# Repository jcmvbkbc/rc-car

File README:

RC car with bidirectional drive and servo steering, controlled by ESP8266.

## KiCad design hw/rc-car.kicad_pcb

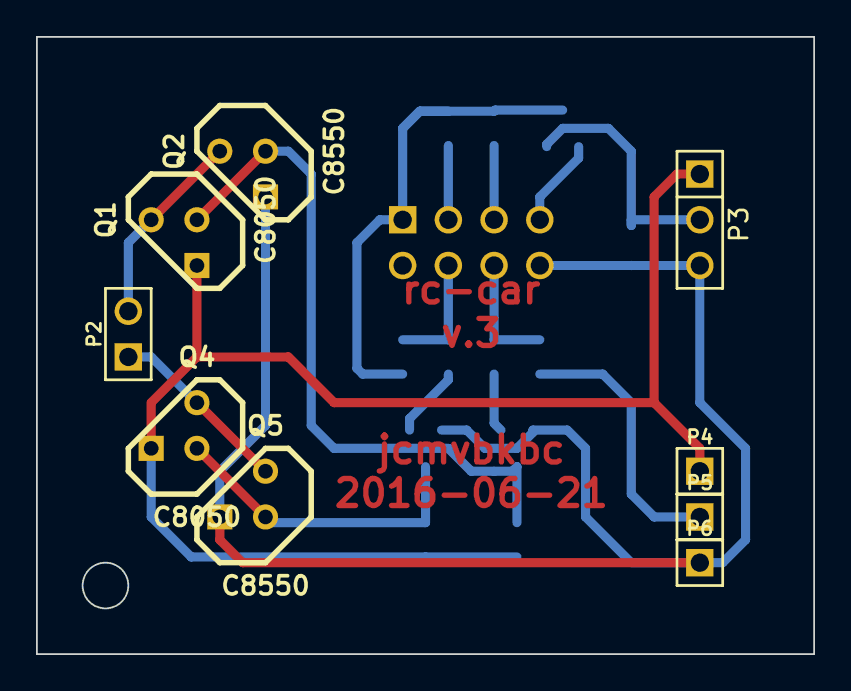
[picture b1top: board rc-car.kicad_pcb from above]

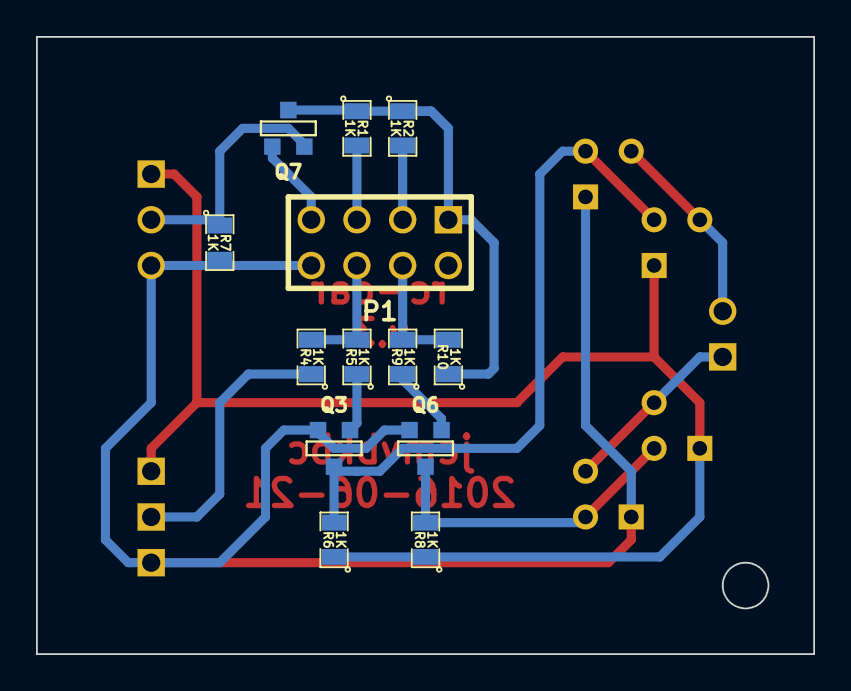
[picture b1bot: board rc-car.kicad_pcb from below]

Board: 2 copper layers, 43.2 x 34.3 mm, 22 parts (13 on the bottom side), 15 nets.

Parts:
P1: CONN_4X2; pin_array_4x2
P2: CONN_2; PIN_ARRAY_2X1
P3: CONN_3; PIN_ARRAY_3X1
P4, P5, P6: CONN_1; PIN_ARRAY_1
Q1, Q4: C8050; TO92-123
Q2, Q5: C8550; TO92-123
Q3, Q6, Q7: MMBT2222; SOT23EBC
R1, R2, R4, R5, R6, R7, R8, R9, R10: 1K; SM0805

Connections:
+3.3V: P1.1, P5.1, Q7.3, R1.1, R2.1, R4.1, R10.1
+5V: P3.1, P4.1, Q1.3, Q4.3, R6.1, R8.1
/BKWD: P1.4, R9.2, R10.2
/FWD: P1.6, R4.2, R5.2
/MN: P2.1, Q4.1, Q5.1
/MP: P2.2, Q1.1, Q2.1
/STEER: P1.7, Q7.2
GND: P1.8, P3.3, P6.1, Q2.3, Q3.1, Q5.3, Q6.1, R7.2
unnamed: Q3.2, R5.1
unnamed: Q6.2, R9.1
unnamed: P3.2, Q7.1, R7.1
unnamed: Q4.2, Q5.2, Q6.3, R8.2
unnamed: P1.3, R2.2
unnamed: P1.5, R1.2
unnamed: Q1.2, Q2.2, Q3.3, R6.2

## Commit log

2016-05-21 initial
2016-05-21 add scheme and footprint associations
2016-05-22 add PCB
2016-05-22 add PCB plots
2016-05-29 fix bidirectional drive bug
2016-05-29 update plots
2016-06-19 sw: initial code
2016-09-30 sw: switch PWM polarity
2016-09-30 hw: update schematic and plots
    - use separate +5V for motors and +3.3V for ESP8266;
    - add power terminals;
    - use two-tact common collector drivers, drive them by common emitter
    voltage amplifiers.
2016-09-30 sw: switch to HW timer
